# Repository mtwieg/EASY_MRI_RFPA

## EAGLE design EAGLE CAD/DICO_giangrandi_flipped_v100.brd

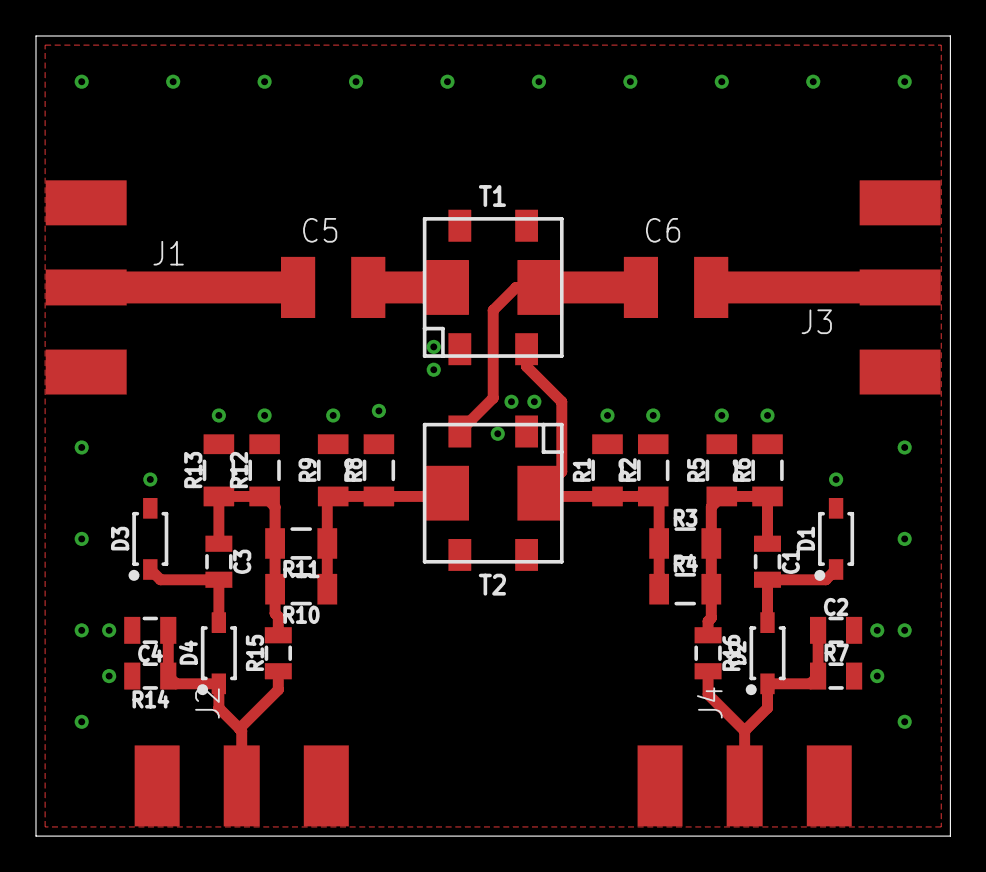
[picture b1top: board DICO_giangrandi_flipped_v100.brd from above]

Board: 2 copper layers, 50.8 x 44.5 mm, 32 parts (0 on the bottom side), 13 nets.

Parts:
C1, C2, C3, C4: 0.1uF; 0805_IPC-7351B
C5, C6: 0.1uF; C1812
D1, D2, D3, D4: D-SCHOTTKY1N5711W-7-FSOD123; SOD123
J1, J2, J3, J4: BNC_EDGE
R1, R2, R3, R4, R5, R6, R8, R9, R10, R11, R12, R13: 1K; 1206_IPC-7351B
R7, R14, R15, R16: 1.0K; 0805_IPC-7351B
T1, T2: TRAFO_CURRENTSENSEPA1005_NOCENTERPADS; PA1005_NOCENTERPADS

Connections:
GND: C2.2, C4.2, D1.A, D3.A, J1.G1, J1.G2, J1.G3, J1.G4, J2.G1, J2.G2, J2.G3, J2.G4, J3.G1, J3.G2, J3.G3, J3.G4, J4.G1, J4.G2, J4.G3, J4.G4, R1.2, R2.2, R5.2, R6.2, R7.2, R8.2, R9.2, R12.2, R13.2, R14.2, T1.1, T2.1
unnamed: R8.1, R9.1, R10.1, R11.1, T2.7
unnamed: C5.2, T1.8
unnamed: C5.1, J1.C
unnamed: C1.1, R3.2, R4.2, R5.1, R6.1, R16.1
unnamed: C1.2, D1.K, D2.A
unnamed: C2.1, D2.K, J4.C, R7.1, R16.2
unnamed: C3.1, R10.2, R11.2, R12.1, R13.1, R15.2
unnamed: C3.2, D3.K, D4.A
unnamed: C4.1, D4.K, J2.C, R14.1, R15.1
unnamed: C6.2, J3.C
unnamed: R1.1, R2.1, R3.1, R4.1, T1.3, T2.8
unnamed: C6.1, T1.7, T2.3

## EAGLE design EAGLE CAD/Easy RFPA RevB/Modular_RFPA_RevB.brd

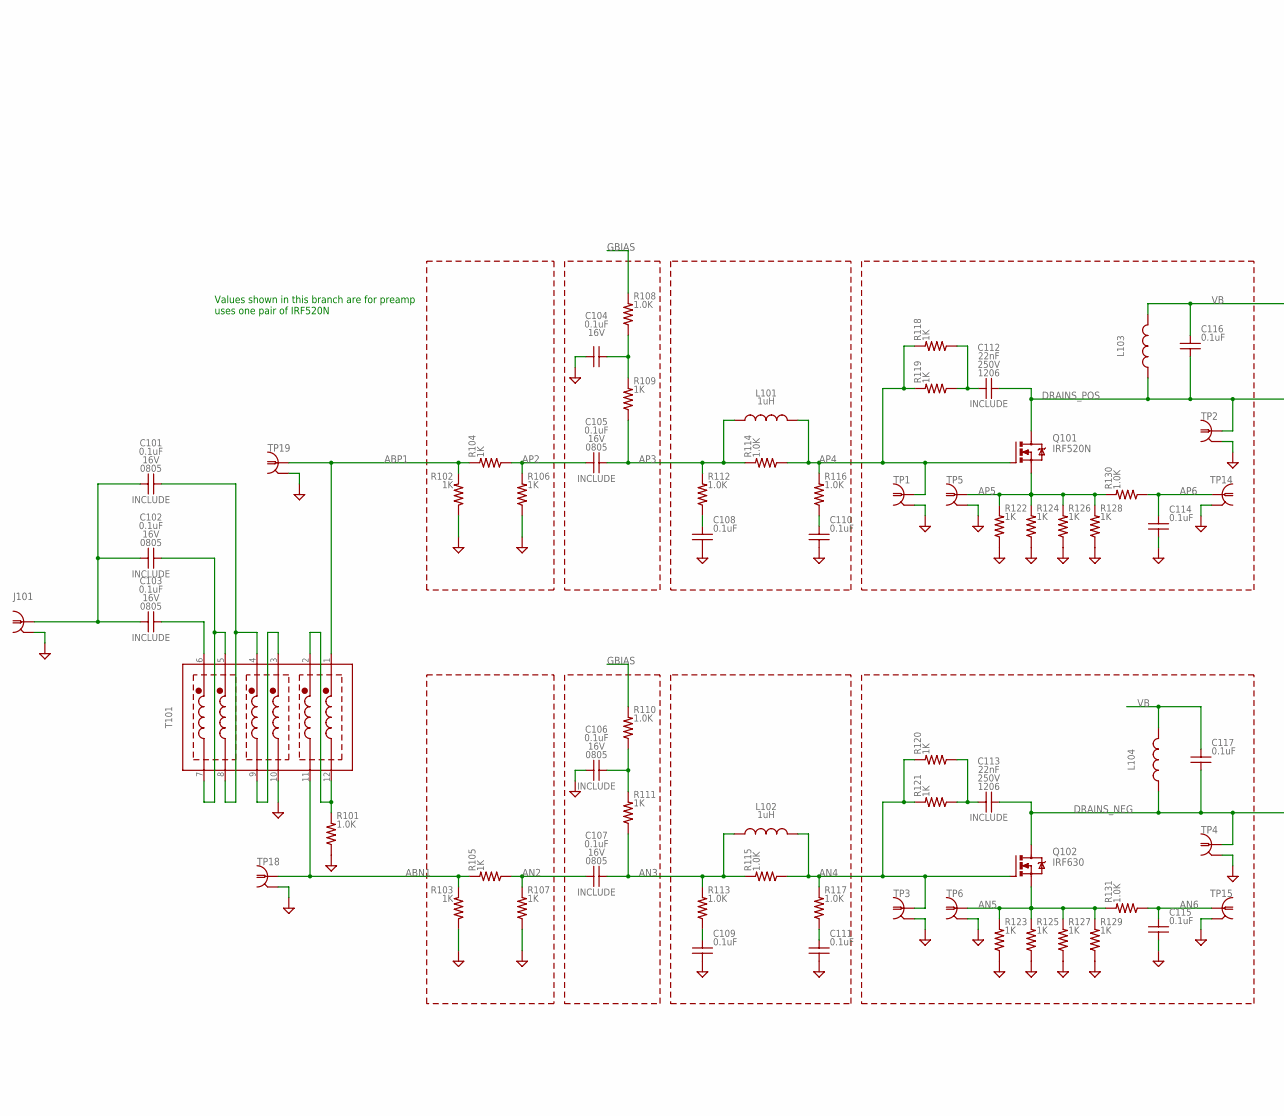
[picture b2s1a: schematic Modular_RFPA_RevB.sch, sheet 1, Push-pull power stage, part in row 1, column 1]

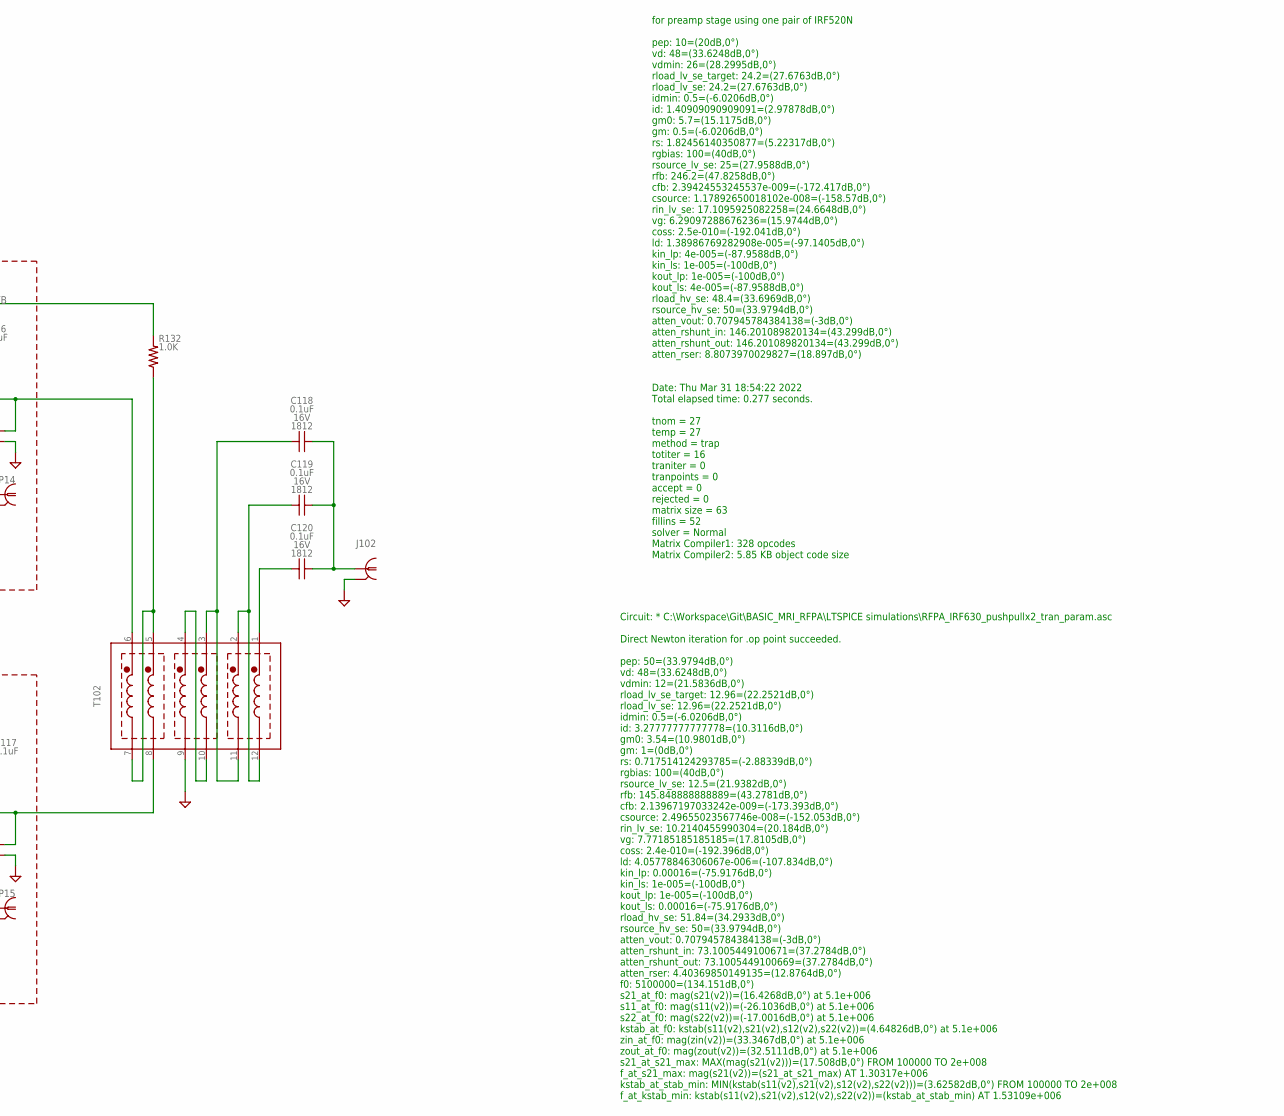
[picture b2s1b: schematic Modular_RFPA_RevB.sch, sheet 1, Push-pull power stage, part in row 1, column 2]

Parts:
C101, C102, C103, C104, C105, C106, C107, C108, C109, C110, C111, C114, C115: 0.1uF; 0805_IPC-7351B
C112, C113: 22nF; C1206
C116, C117, C118, C119, C120: 0.1uF; C1812
J101, J102: COAXBNC_EDGE; BNC_EDGE
L101, L102: 1uH; L1008
L103, L104: L; DR127
Q101: IRF520N; TO220BV
Q102: IRF630; TO220BV
R101, R108, R110, R112, R113, R114, R115, R116, R117, R130, R131, R132: 1.0K; 0805_IPC-7351B
R102, R103, R104, R105, R106, R107, R109, R111: 1K; R1206
R118, R119, R120, R121, R122, R123, R124, R125, R126, R127, R128, R129: 1K; R2512
T101, T102: HP4_TRAFO; HP4
TP1, TP3, TP14, TP15, TP18, TP19: PROBE_TPTP_5MM; PROBE_TP_5MM
TP2, TP4, TP5, TP6: PROBE_TPTP_7P5MM; PROBE_TP_7P5MM

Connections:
ABN1: R103.1, R105.1, T101.11 (F2), TP18.TP (1); also elsewhere on the board
ABP1: R102.1, R104.1, T101.1 (S1), TP19.TP (1); also elsewhere on the board
AN2: C107.2, R105.2, R107.1
AN3: C107.1, L102.1, R111.2, R113.1, R115.1
AN4: L102.2, Q102.G, R115.2, R117.1, R120.1, R121.1, TP3.TP (1)
AN5: Q102.S, R123.1, R125.1, R127.1, R129.1, R131.1, TP6.TP (1)
AN6: C115.1, R131.2, TP15.TP (1)
AP2: C105.2, R104.2, R106.1
AP3: C105.1, L101.1, R109.2, R112.1, R114.1
AP4: L101.2, Q101.G, R114.2, R116.1, R118.1, R119.1, TP1.TP (1)
AP5: Q101.S, R122.1, R124.1, R126.1, R128.1, R130.1, TP5.TP (1)
AP6: C114.1, R130.2, TP14.TP (1)
DRAINS_NEG: C113.2, C117.2, L104.1, Q102.D, T102.8 (F5), TP4.TP (1); also elsewhere on the board
DRAINS_POS: C112.2, C116.2, L103.1, Q101.D, T102.6 (S6), TP2.TP (1); also elsewhere on the board
GBIAS: R108.1, R110.1; also elsewhere on the board
GND: C104.2, C106.2, C108.2, C109.2, C110.2, C111.2, C114.2, C115.2, J101.G1 (GND1), J101.G2 (GND1), J101.G3 (GND1), J101.G4 (GND1), J102.G1 (GND1), J102.G2 (GND1), J102.G3 (GND1), J102.G4 (GND1), R101.2, R102.2, R103.2, R106.2, R107.2, R122.2, R123.2, R124.2, R125.2, R126.2, R127.2, R128.2, R129.2, T101.10 (F3), T102.9 (F4), TP1.GND (GND1), TP2.GND (GND1), TP3.GND (GND1), TP4.GND (GND1), TP5.GND (GND1), TP6.GND (GND1), TP14.GND (GND1), TP15.GND (GND1), TP18.GND (GND1), TP19.GND (GND1); also elsewhere on the board
unnamed: C113.1, R120.2, R121.2
unnamed: C109.1, R113.2
unnamed: C104.1, R108.2, R109.1
unnamed: C108.1, R112.2
unnamed: C110.1, R116.2
unnamed: C112.1, R118.2, R119.2
unnamed: C106.1, R110.2, R111.1
unnamed: C111.1, R117.2
unnamed: T101.3 (S3), T101.9 (F4)
unnamed: R101.1, T101.2 (S2), T101.12 (F1)
unnamed: C119.1, T102.2 (S2), T102.12 (F1)
unnamed: C120.1, T102.1 (S1)
unnamed: C118.2, C119.2, C120.2, J102.C (1)
unnamed: C101.2, C102.2, C103.2, J101.C (1)
unnamed: C103.1, T101.6 (S6)
unnamed: C118.1, T102.3 (S3), T102.11 (F2)
unnamed: C101.1, T101.4 (S4), T101.8 (F5)
unnamed: T102.4 (S4), T102.10 (F3)
VB: C116.1, C117.1, L103.2, L104.2, R132.1; also elsewhere on the board
VB_CT: R132.2, T102.5 (S5), T102.7 (F6)
VB_CT1: C102.1, T101.5 (S5), T101.7 (F6)

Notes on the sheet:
for preamp stage using one pair of IRF520N pep: 10=(20dB,0°) vd: 48=(33.6248dB,0°) vdmin: 26=(28.2995dB,0°) rload_lv_se_target: 24.2=(27.6763dB,0°) rload_lv_se: 24.2=(27.6763dB,0°) idmin: 0.5=(-6.0206dB,0°) id: 1.40909090909091=(2.97878dB,0°) gm0: 5.7=(15.1175dB,0°) gm: 0.5=(-6.0206dB,0°) rs: 1.824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
Values shown in this branch are for preamp uses one pair of IRF520N
Circuit: * C:\Workspace\Git\BASIC_MRI_RFPA\LTSPICE simulations\RFPA_IRF630_pushpullx2_tran_param.asc Direct Newton iteration for .op point succeeded. pep: 50=(33.9794dB,0°) vd: 48=(33.6248dB,0°) vdmin: 12=(21.5836dB,0°) rload_lv_se_target: 12.96=(22.2521dB,0°) rload_lv_se: 12.96=(22.2521dB,0°) idmi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

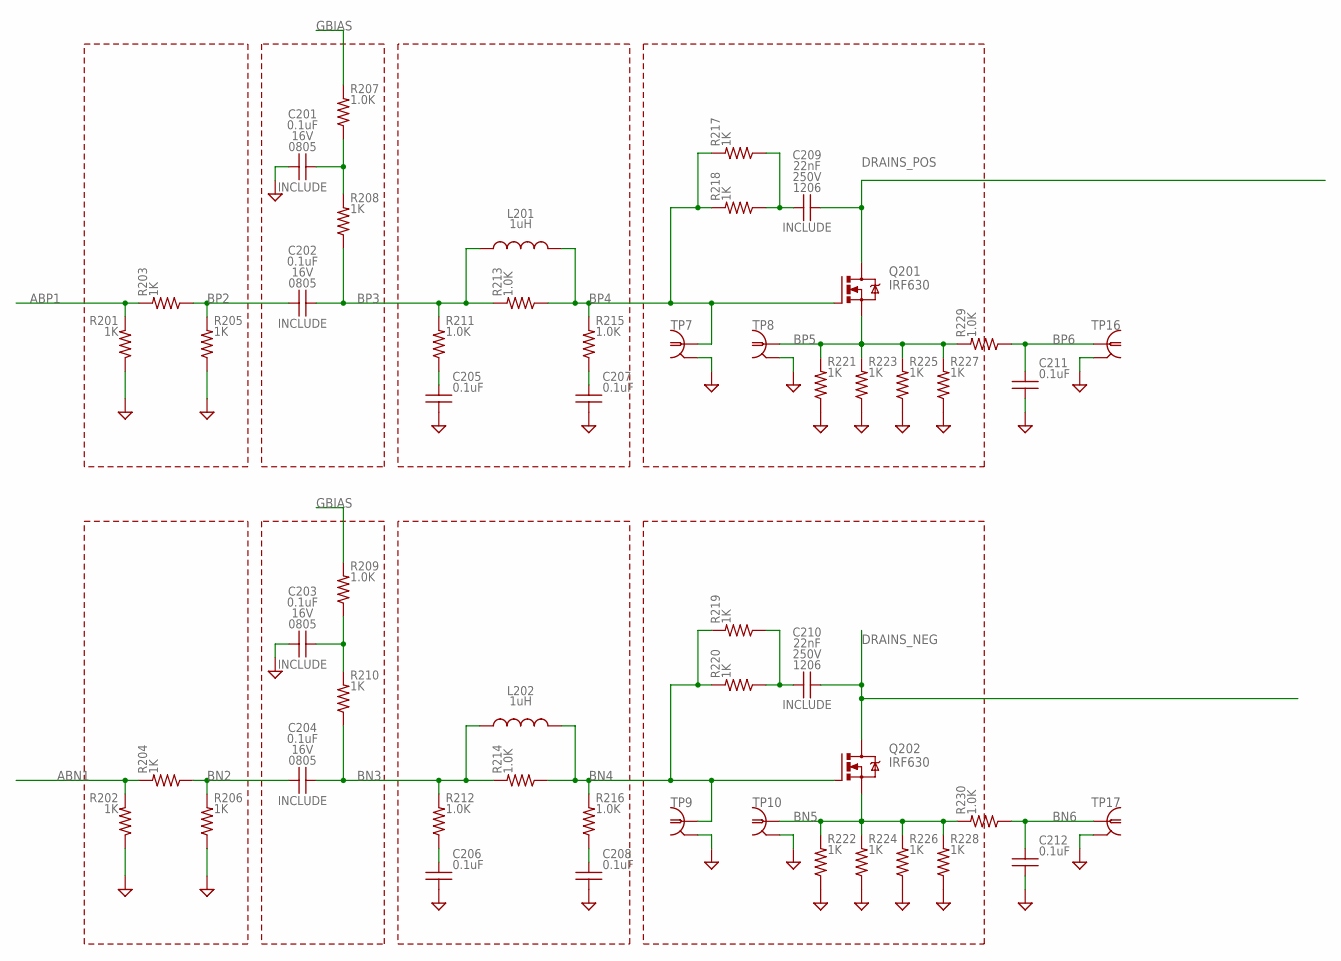
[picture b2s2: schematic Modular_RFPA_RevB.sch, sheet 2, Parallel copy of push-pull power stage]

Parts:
C201, C202, C203, C204, C205, C206, C207, C208, C211, C212: 0.1uF; 0805_IPC-7351B
C209, C210: 22nF; C1206
L201, L202: 1uH; L1008
Q201, Q202: IRF630; TO220BV
R201, R202, R203, R204, R205, R206, R208, R210: 1K; R1206
R207, R209, R211, R212, R213, R214, R215, R216, R229, R230: 1.0K; 0805_IPC-7351B
R217, R218, R219, R220, R221, R222, R223, R224, R225, R226, R227, R228: 1K; R2512
TP7, TP9, TP10, TP16: PROBE_TPTP_5MM; PROBE_TP_5MM
TP8, TP17: PROBE_TPTP_7P5MM; PROBE_TP_7P5MM

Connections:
ABN1: R202.1, R204.1; also elsewhere on the board
ABP1: R201.1, R203.1; also elsewhere on the board
BN2: C204.2, R204.2, R206.1
BN3: C204.1, L202.1, R210.2, R212.1, R214.1
BN4: L202.2, Q202.G, R214.2, R216.1, R219.1, R220.1, TP9.TP (1)
BN5: Q202.S, R222.1, R224.1, R226.1, R228.1, R230.1, TP10.TP (1)
BN6: C212.1, R230.2, TP17.TP (1)
BP2: C202.2, R203.2, R205.1
BP3: C202.1, L201.1, R208.2, R211.1, R213.1
BP4: L201.2, Q201.G, R213.2, R215.1, R217.1, R218.1, TP7.TP (1)
BP5: Q201.S, R221.1, R223.1, R225.1, R227.1, R229.1, TP8.TP (1)
BP6: C211.1, R229.2, TP16.TP (1)
DRAINS_NEG: C210.2, Q202.D; also elsewhere on the board
DRAINS_POS: C209.2, Q201.D; also elsewhere on the board
GBIAS: R207.1, R209.1; also elsewhere on the board
GND: C201.2, C203.2, C205.2, C206.2, C207.2, C208.2, C211.2, C212.2, R201.2, R202.2, R205.2, R206.2, R221.2, R222.2, R223.2, R224.2, R225.2, R226.2, R227.2, R228.2, TP7.GND (GND1), TP8.GND (GND1), TP9.GND (GND1), TP10.GND (GND1), TP16.GND (GND1), TP17.GND (GND1); also elsewhere on the board
unnamed: C203.1, R209.2, R210.1
unnamed: C206.1, R212.2
unnamed: C208.1, R216.2
unnamed: C210.1, R219.2, R220.2
unnamed: C201.1, R207.2, R208.1
unnamed: C205.1, R211.2
unnamed: C207.1, R215.2
unnamed: C209.1, R217.2, R218.2

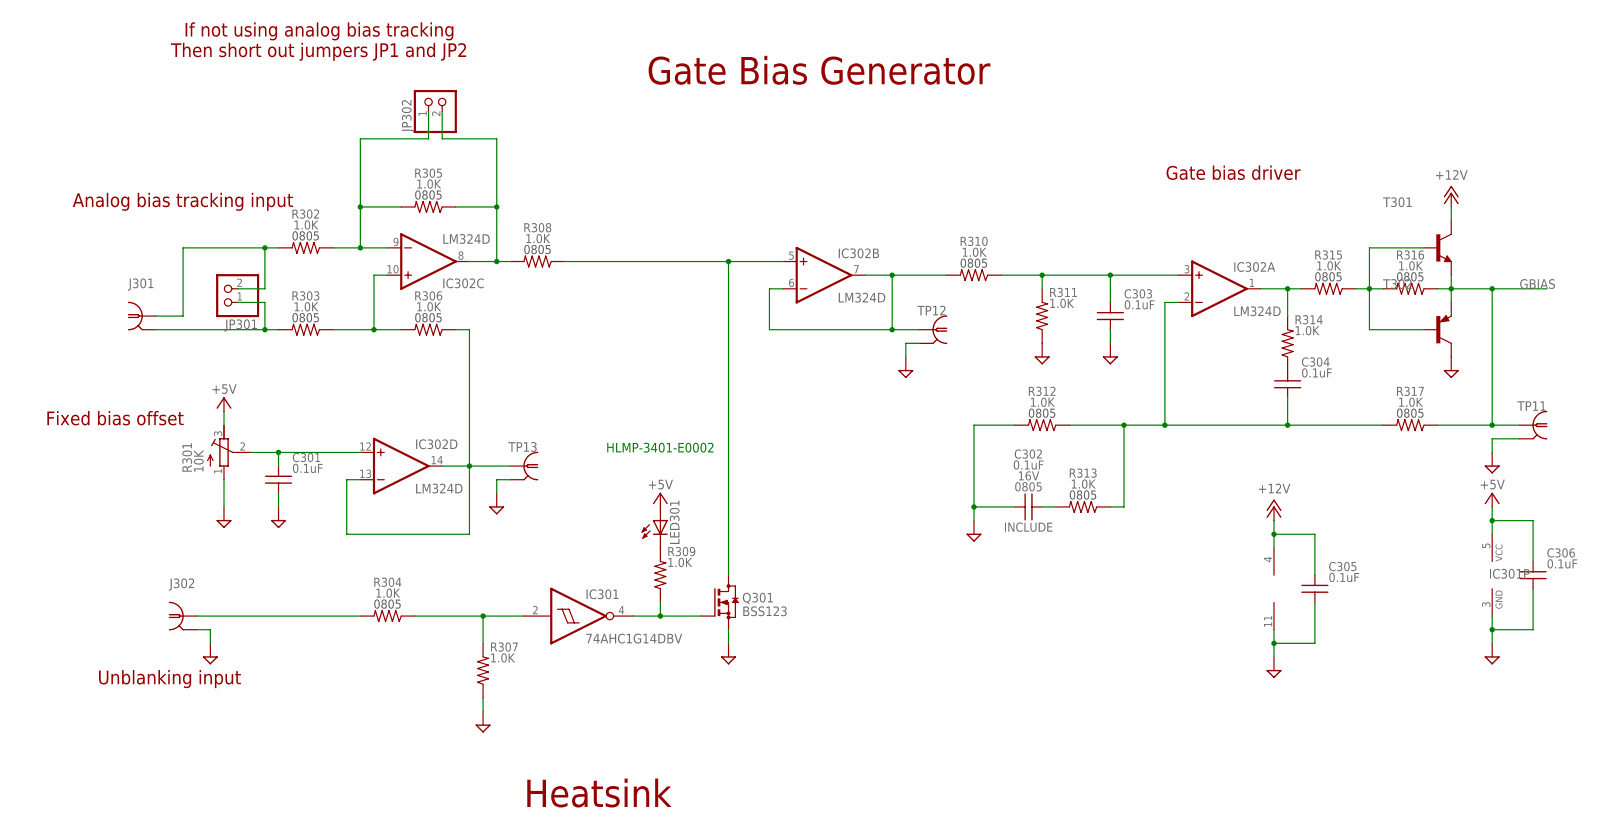
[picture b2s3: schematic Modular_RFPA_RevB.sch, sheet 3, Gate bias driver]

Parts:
C301, C302, C303, C304, C305, C306: 0.1uF; 0805_IPC-7351B
IC301: 74AHC1G14DBV; SOT23-5
IC302: LM324D; SO14
J301, J302: COAXBNC_EDGE; BNC_EDGE
JP301, JP302: PINHD-1X2; 1X02
LED301: LED5MM
Q301: BSS123; SOT23
R301: 10K; RTRIM3299W
R302, R303, R304, R305, R306, R307, R308, R309, R310, R311, R312, R313, R314, R315, R316, R317: 1.0K; 0805_IPC-7351B
T301: BC808-NPN-SOT23-BEC; SOT23-BEC
T302: BC807-16-PNP-SOT23-BEC; SOT23-BEC
TP11, TP12, TP13: PROBE_TPTP_5MM; PROBE_TP_5MM

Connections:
+5V: C306.1, IC301.5 (VCC), LED301.A, R301.3 (E); also elsewhere on the board
+12V: C305.1, IC302.4 (V+), T301.C; also elsewhere on the board
GBIAS: R316.2, R317.2, T301.E, T302.E, TP11.TP (1); also elsewhere on the board
GND: C301.2, C302.2, C303.2, C305.2, C306.2, IC301.3 (GND), IC302.11 (V-), J302.G1 (GND1), J302.G2 (GND1), J302.G3 (GND1), J302.G4 (GND1), Q301.2 (S), R301.1 (A), R307.2, R311.2, R312.1, T302.C, TP11.GND (GND1), TP12.GND (GND1), TP13.GND (GND1); also elsewhere on the board
unnamed: IC302.1 (OUT), R314.1, R315.1
unnamed: R315.2, R316.1, T301.B, T302.B
unnamed: IC301.2 (I), R304.2, R307.1
unnamed: IC302.6 (-IN), IC302.7 (OUT), R310.1, TP12.TP (1)
unnamed: C304.1, R314.2
unnamed: C302.1, R313.1
unnamed: C304.2, IC302.2 (-IN), R312.2, R313.2, R317.1
unnamed: C303.1, IC302.3 (+IN), R310.2, R311.1
unnamed: IC302.10 (+IN), R303.2, R306.1
unnamed: IC302.8 (OUT), JP302.2, R305.2, R308.1
unnamed: IC302.9 (-IN), JP302.1, R302.2, R305.1
unnamed: J301.C (1), JP301.2, R302.1
unnamed: J301.G1 (GND1), J301.G2 (GND1), J301.G3 (GND1), J301.G4 (GND1), JP301.1, R303.1
unnamed: IC302.5 (+IN), Q301.3 (D), R308.2
unnamed: IC301.4 (O), Q301.1 (G), R309.2
unnamed: C301.1, IC302.12 (+IN), R301.2 (S)
unnamed: IC302.13 (-IN), IC302.14 (OUT), R306.2, TP13.TP (1)
unnamed: LED301.K (C), R309.1
unnamed: J302.C (1), R304.1

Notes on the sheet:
Gate Bias Generator
Heatsink
If not using analog bias tracking Then short out jumpers JP1 and JP2
Analog bias tracking input
Fixed bias offset
Gate bias driver
Unblanking input
‎HLMP-3401-E0002‎

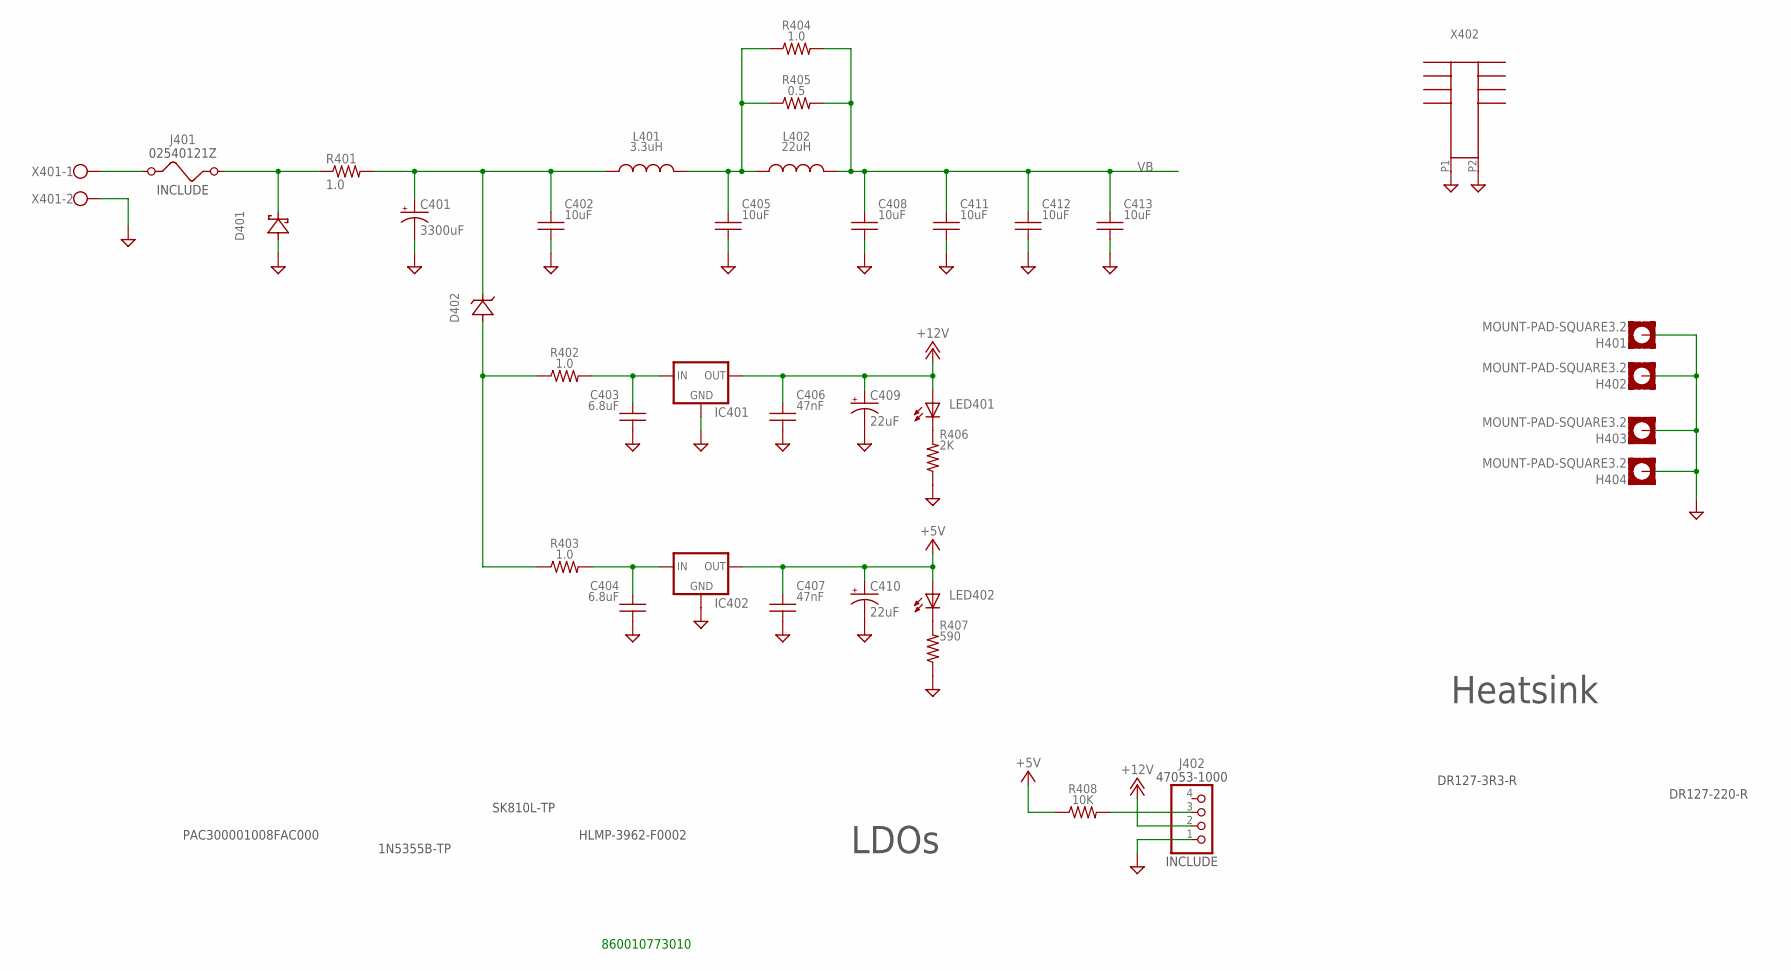
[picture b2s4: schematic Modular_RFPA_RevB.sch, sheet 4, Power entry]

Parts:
C401: 3300uF; EB25D
C402, C405, C408, C411, C412, C413: 10uF; C2220_CKG57N
C403, C404: 6.8uF; C1210
C406, C407: 47nF; C1206
C409, C410: 22uF; E2,5-7
D401: D-SCHOTTKYSK810L-TPSMC; DO-214AB(SMC)
D402: D-ZENER1N5355B-TPDO15-12; DO15-12
H401, H402, H403, H404: MOUNT-PAD-SQUARE3.2; 3,2-PAD-SQUARE
IC401, IC402: 78XXS
J401: FUSE_2P; 02540121Z
J402: KK_PCFAN; 47053-1000
L401: 3.3uH; DR127
L402: 22uH; DR127
LED401, LED402: LED5MM
R401: 1.0; P0817V
R402, R403, R404: 1.0; R1206
R405: 0.5; R1206
R406: 2K; 0805_IPC-7351B
R407: 590; 0805_IPC-7351B
R408: 10K; 0805_IPC-7351B
X401: W237-102
X402: HEATSINK_OMNI_DUAL30-75-D; OMNI-UNI-30-75-D

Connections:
+5V: C407.1, C410.+, IC402.OUT, LED402.A, R408.1; also elsewhere on the board
+12V: C406.1, C409.+, IC401.OUT, J402.2, LED401.A; also elsewhere on the board
GND: C401.-, C402.2, C403.2, C404.2, C405.2, C406.2, C407.2, C408.2, C409.-, C410.-, C411.2, C412.2, C413.2, D401.A (A1), H401.B3,2, H402.B3,2, H403.B3,2, H404.B3,2, IC401.GND, IC402.GND, J402.1, R406.2, R407.2, X401.2, X402.P1, X402.P2; also elsewhere on the board
unnamed: D402.A (A1), R402.1, R403.1
unnamed: LED401.K (C), R406.1
unnamed: LED402.K (C), R407.1
unnamed: C403.1, IC401.IN, R402.2
unnamed: D401.K (C1), J401.2, R401.1
unnamed: J401.1, X401.1
unnamed: C401.+, C402.1, D402.C (C1), L401.1, R401.2
unnamed: C405.1, L401.2, L402.1, R404.1, R405.1
unnamed: C404.1, IC402.IN, R403.2
unnamed: J402.3, R408.2
VB: C408.1, C411.1, C412.1, C413.1, L402.2, R404.2, R405.2; also elsewhere on the board

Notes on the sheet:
LDOs
Heatsink
PAC300001008FAC000
DR127-220-R
DR127-3R3-R
1N5355B-TP
HLMP-3962-F0002‎
860010773010
SK810L-TP

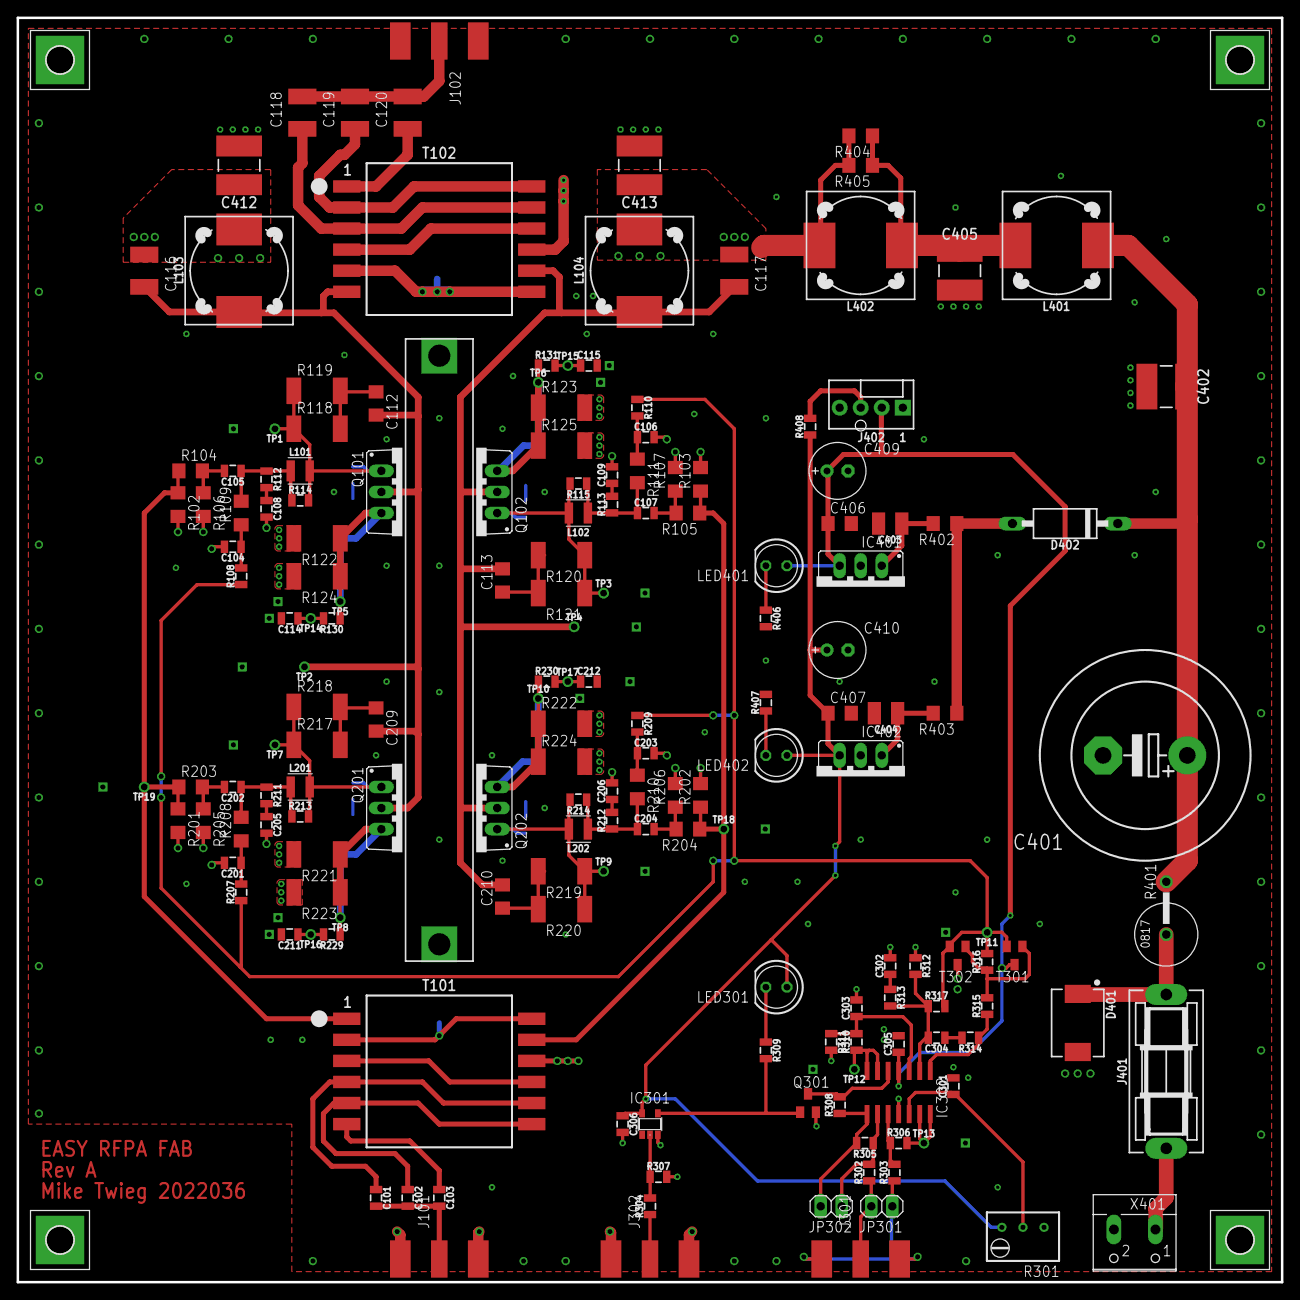
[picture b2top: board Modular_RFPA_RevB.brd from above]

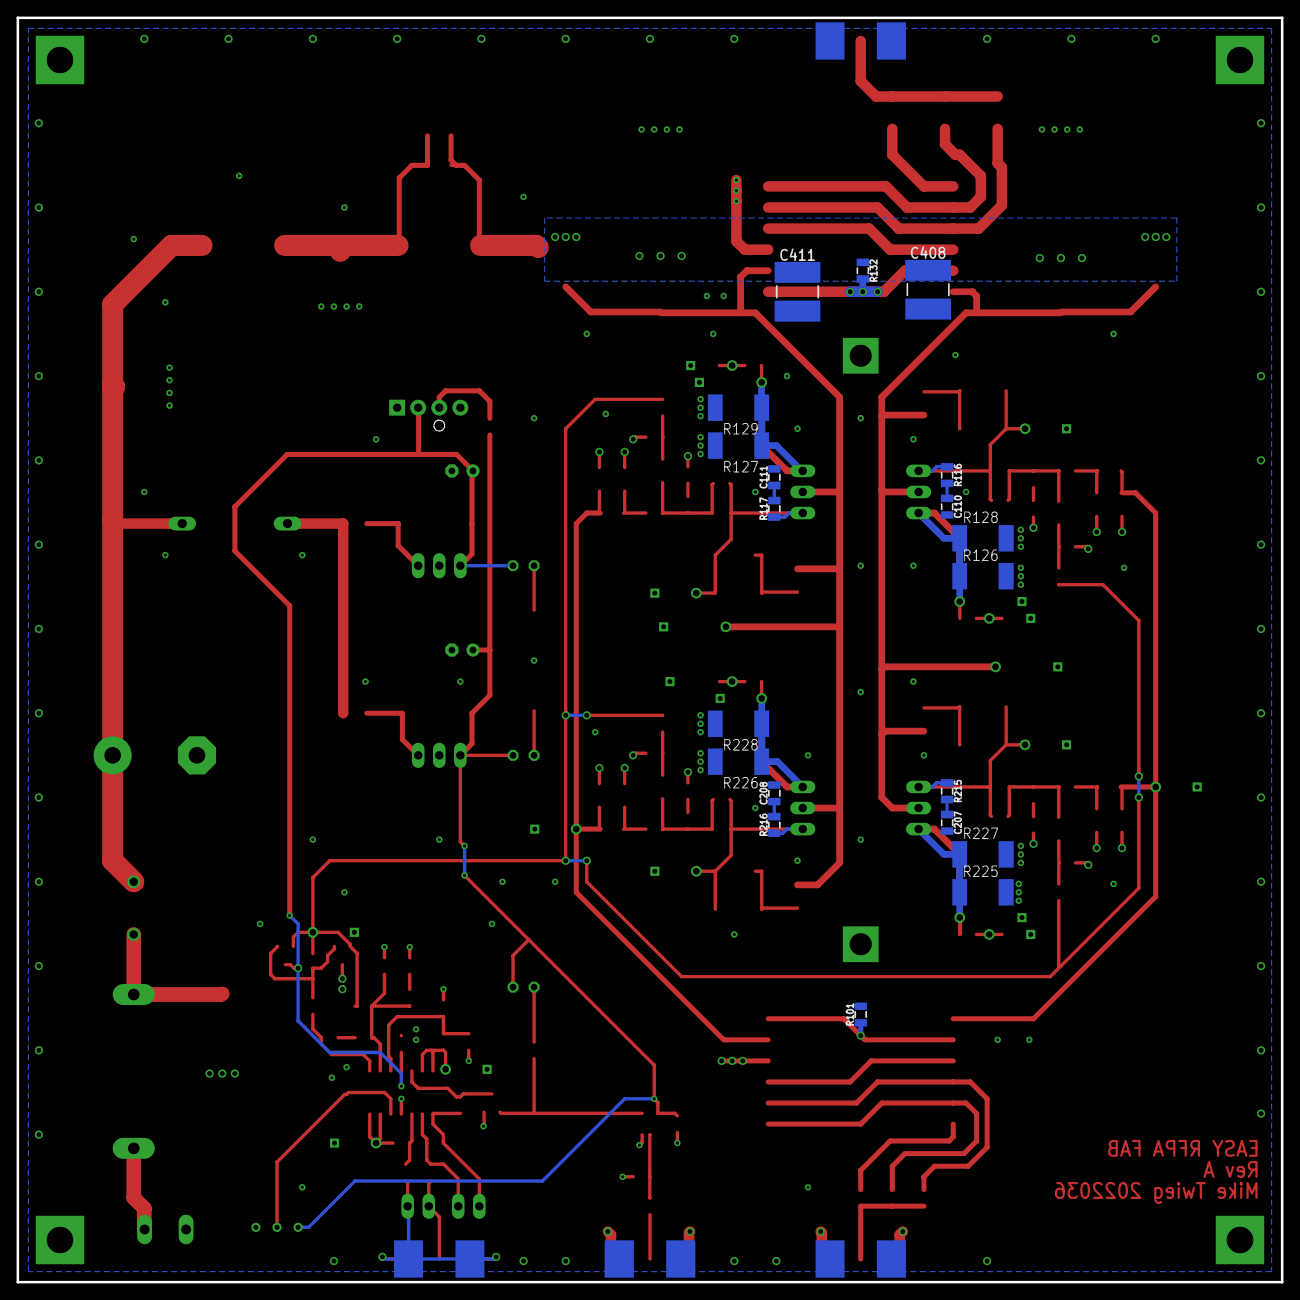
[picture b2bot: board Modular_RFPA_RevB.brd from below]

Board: 4 copper layers, 152.4 x 152.4 mm, 197 parts (20 on the bottom side), 86 nets.

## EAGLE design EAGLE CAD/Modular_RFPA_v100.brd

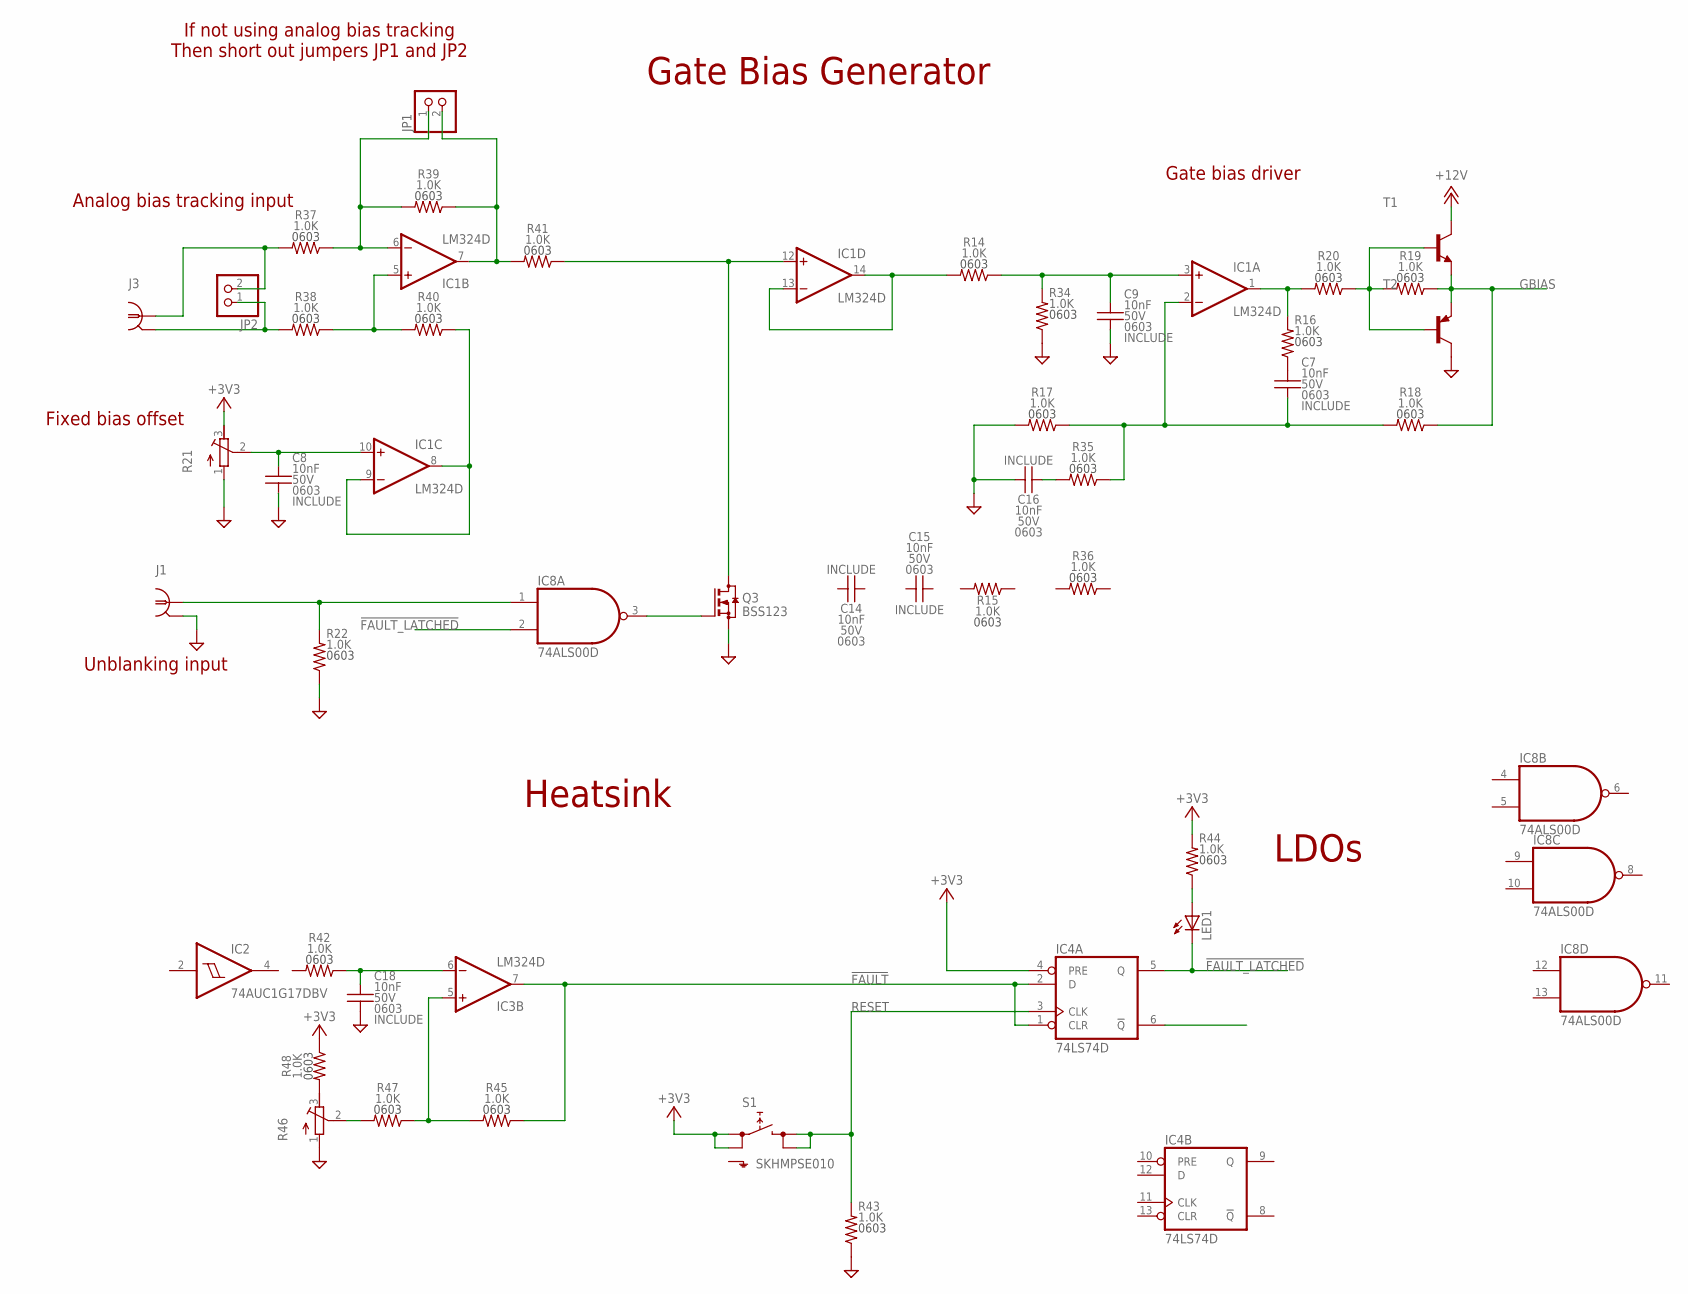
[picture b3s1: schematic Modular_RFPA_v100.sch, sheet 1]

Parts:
C7, C8, C9, C14, C15, C16, C18: 10nF; 0603_IPC-7351B
IC1, IC3: LM324D; SO14
IC2: 74AUC1G17DBV; SOT23-5
IC4: 74LS74D; SO14
IC8: 74ALS00D; SO14
J1, J3: COAXBNC_EDGE; BNC_EDGE
JP1, JP2: PINHD-1X2; 1X02
LED1: LED5MM
Q3: BSS123; SOT23
R14, R15, R16, R17, R18, R19, R20, R22, R34, R35, R36, R37, R38, R39, R40, R41, R42, R43, R44, R45, R47, R48: 1.0K; 0603_IPC-7351B
R21, R46: R-TRIMM3299W; RTRIM3299W
S1: SKHMPSE010; SKHMPXE010
T1: BC808-NPN-SOT23-BEC; SOT23-BEC
T2: BC807-16-PNP-SOT23-BEC; SOT23-BEC

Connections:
!FAULT: IC3.7 (OUT), IC4.1 (CLR), IC4.2 (D), R45.2
!FAULT_LATCHED: IC4.5 (Q), IC8.2 (I1), LED1.K (C)
+3V3: IC4.4 (PRE), R21.3 (E), R44.1, R48.2, S1.1 (1.1), S1.2 (1.2)
+12V: T1.C; also elsewhere on the board
GBIAS: R18.2, R19.2, T1.E, T2.E; also elsewhere on the board
GND: C8.2, C9.2, C16.1, C18.2, IC2.3 (GND), IC4.7 (GND), IC8.7 (GND), J1.G1 (GND1), J1.G2 (GND1), J1.G3 (GND1), J1.G4 (GND1), Q3.2 (S), R17.1, R21.1 (A), R22.2, R34.2, R43.2, R46.1 (A), T2.C; also elsewhere on the board
unnamed: IC1.1 (OUT), R16.1, R20.1
unnamed: R19.1, R20.2, T1.B, T2.B
unnamed: IC8.1 (I0), J1.C (1), R22.1
unnamed: IC1.13 (-IN), IC1.14 (OUT), R14.1
unnamed: C7.1, R16.2
unnamed: C16.2, R35.1
unnamed: C7.2, IC1.2 (-IN), R17.2, R18.1, R35.2
unnamed: C9.1, IC1.3 (+IN), R14.2, R34.1
unnamed: IC1.5 (+IN), R38.2, R40.1
unnamed: IC1.7 (OUT), JP1.2, R39.2, R41.1
unnamed: IC1.6 (-IN), JP1.1, R37.2, R39.1
unnamed: J3.C (1), JP2.2, R37.1
unnamed: J3.G1 (GND1), J3.G2 (GND1), J3.G3 (GND1), J3.G4 (GND1), JP2.1, R38.1
unnamed: IC1.12 (+IN), Q3.3 (D), R41.2
unnamed: C8.1, IC1.10 (+IN), R21.2 (S)
unnamed: IC1.8 (OUT), IC1.9 (-IN), R40.2
unnamed: C18.1, IC3.6 (-IN), R42.2
unnamed: LED1.A, R44.2
unnamed: IC3.5 (+IN), R45.1, R47.2
unnamed: R46.2 (S), R47.1
unnamed: R46.3 (E), R48.1
RESET: IC4.3 (CLK), R43.1, S1.3 (2.1), S1.4 (2.2)
V+: IC1.4 (V+), IC3.4 (V+)
V-: IC1.11 (V-), IC3.11 (V-)
VCC: IC2.5 (VCC), IC4.14 (VCC), IC8.14 (VCC)

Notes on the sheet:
Gate Bias Generator
LDOs
Heatsink
If not using analog bias tracking Then short out jumpers JP1 and JP2
Analog bias tracking input
Fixed bias offset
Gate bias driver
Unblanking input
